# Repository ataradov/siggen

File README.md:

# SigGen

SigGen is a 100+ MHz signal generator (square wave only) and frequency counter based on Atmel SAM D11.

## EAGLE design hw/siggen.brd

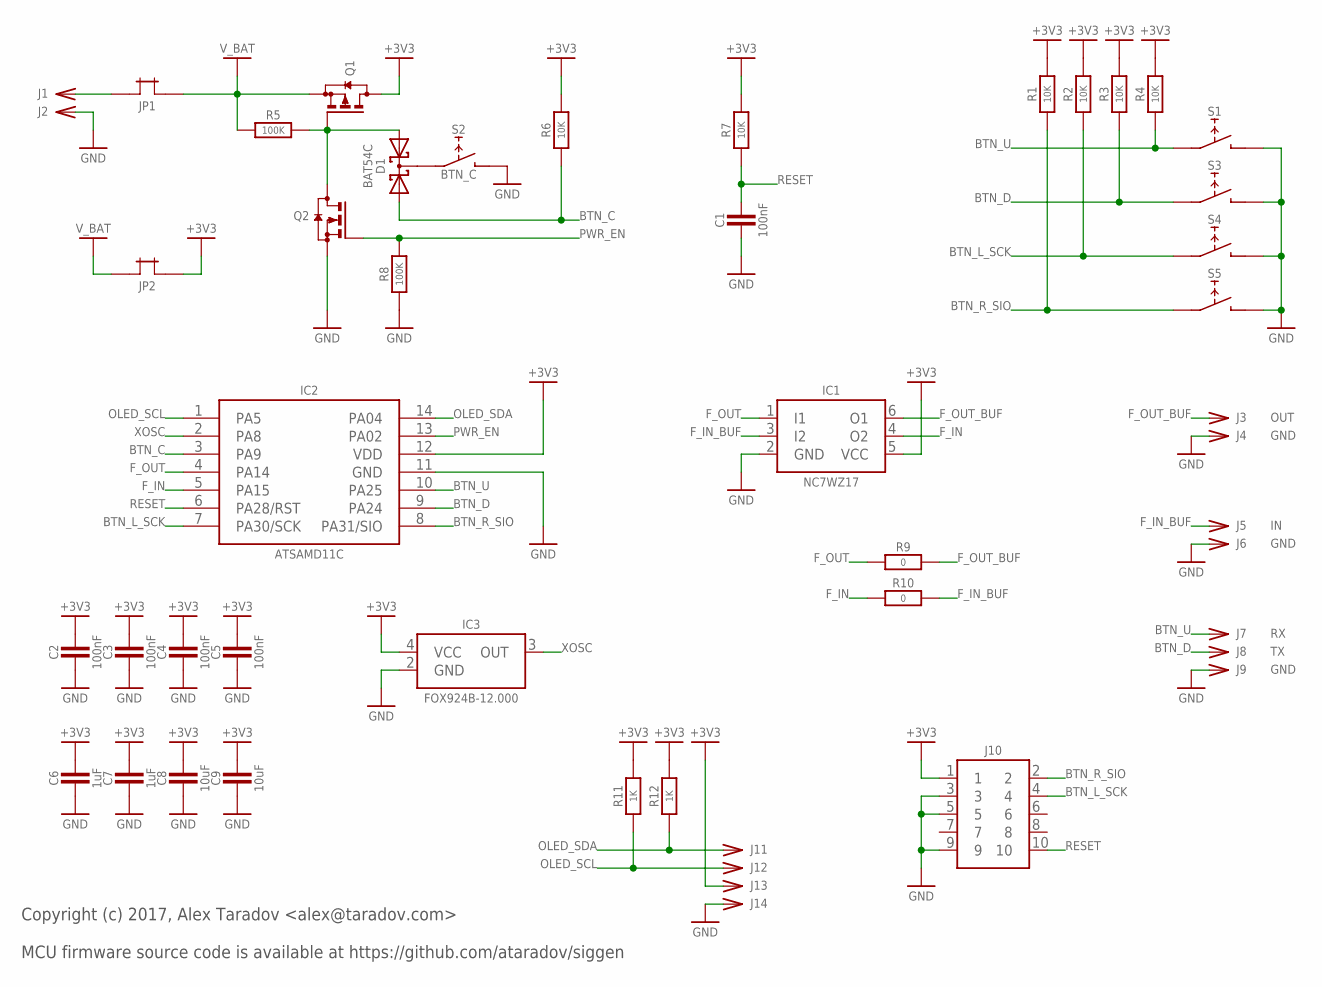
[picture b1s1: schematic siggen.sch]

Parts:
C1, C2, C3, C4, C5: 100nF; SMD0603
C6, C7: 1uF; SMD0603
C8, C9: 10uF; SMD0805
D1: BAT54C; SOT23
IC1: NC7WZ17; SC70
IC2: ATSAMD11C; SO-14
IC3: FOX924B-12.000; CTS406
J1, J2, J11, J12, J13, J14: CONN-SINGLE-TH; PIN-TH
J3: OUT; PIN-TH
J4, J6, J9: GND; PIN-TH
J5: IN; PIN-TH
J7: RX; PIN-TH
J8: TX; PIN-TH
J10: HEADER-5X2-TH-1.27; HEADER-5X2-1.27MM
JP1, JP2: JUMPER-TH-TH; JUMPER-TH
Q1: P-MOSFET; SOT23
Q2: N-MOSFET; SOT23
R1, R2, R3, R4, R6, R7: 10K; SMD0603
R5, R8: 100K; SMD0603
R9, R10: 0; SMD0603
R11, R12: 1K; SMD0603
S1, S3, S4, S5: TACT_SWITCH_6MM-SMD; TACT-SMD-6MM
S2: BTN_C; TACT-SMD-6MM

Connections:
+3V3: C2.2, C3.2, C4.2, C5.2, C6.2, C7.2, C8.2, C9.2, IC1.5 (VCC), IC2.12 (VDD), IC3.4 (VCC), J10.1, J13.1, JP2.2, Q1.3 (D), R1.2, R2.2, R3.2, R4.2, R6.2, R7.2, R11.2, R12.2
BTN_C: D1.1 (A1), IC2.3 (PA9), R6.1
BTN_D: IC2.9 (PA24), J8.1, R3.1, S3.1, S3.2 (1)
BTN_L_SCK: IC2.7 (PA30/SCK), J10.4, R2.1, S4.1, S4.2 (1)
BTN_R_SIO: IC2.8 (PA31/SIO), J10.2, R1.1, S5.1, S5.2 (1)
BTN_U: IC2.10 (PA25), J7.1, R4.1, S1.1, S1.2 (1)
F_IN: IC1.4 (O2), IC2.5 (PA15), R10.1
F_IN_BUF: IC1.3 (I2), J5.1, R10.2
F_OUT: IC1.1 (I1), IC2.4 (PA14), R9.1
F_OUT_BUF: IC1.6 (O1), J3.1, R9.2
GND: C1.1, C2.1, C3.1, C4.1, C5.1, C6.1, C7.1, C8.1, C9.1, IC1.2 (GND), IC2.11 (GND), IC3.2 (GND), J2.1, J4.1, J6.1, J9.1, J10.3, J10.5, J10.9, J14.1, Q2.2 (S), R8.1, S1.3 (2), S1.4 (2), S2.3 (2), S2.4 (2), S3.3 (2), S3.4 (2), S4.3 (2), S4.4 (2), S5.3 (2), S5.4 (2)
unnamed: D1.2 (A2), Q1.1 (G), Q2.3 (D), R5.2
unnamed: D1.3 (CC), S2.1, S2.2 (1)
unnamed: J1.1, JP1.1
OLED_SCL: IC2.1 (PA5), J12.1, R11.1
OLED_SDA: IC2.14 (PA04), J11.1, R12.1
PWR_EN: IC2.13 (PA02), Q2.1 (G), R8.2
RESET: C1.2, IC2.6 (PA28/RST), J10.10, R7.1
V_BAT: JP1.2, JP2.1, Q1.2 (S), R5.1
XOSC: IC2.2 (PA8), IC3.3 (OUT)

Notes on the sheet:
Copyright (c) 2017, Alex Taradov <alex@taradov.com> MCU firmware source code is available at https://github.com/ataradov/siggen

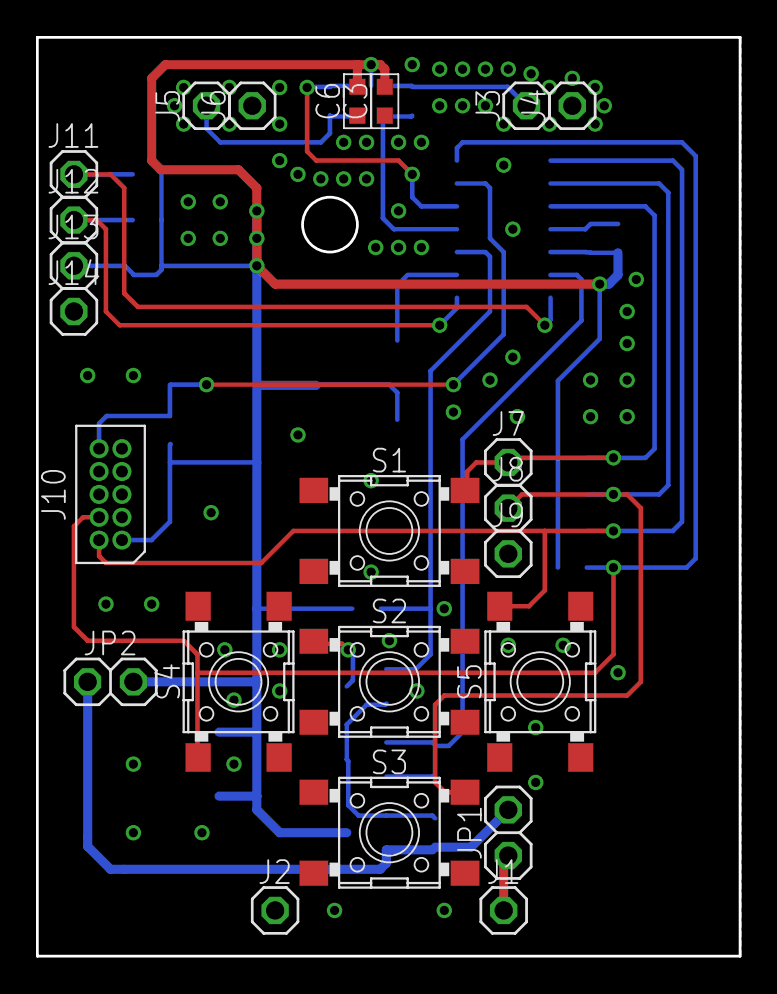
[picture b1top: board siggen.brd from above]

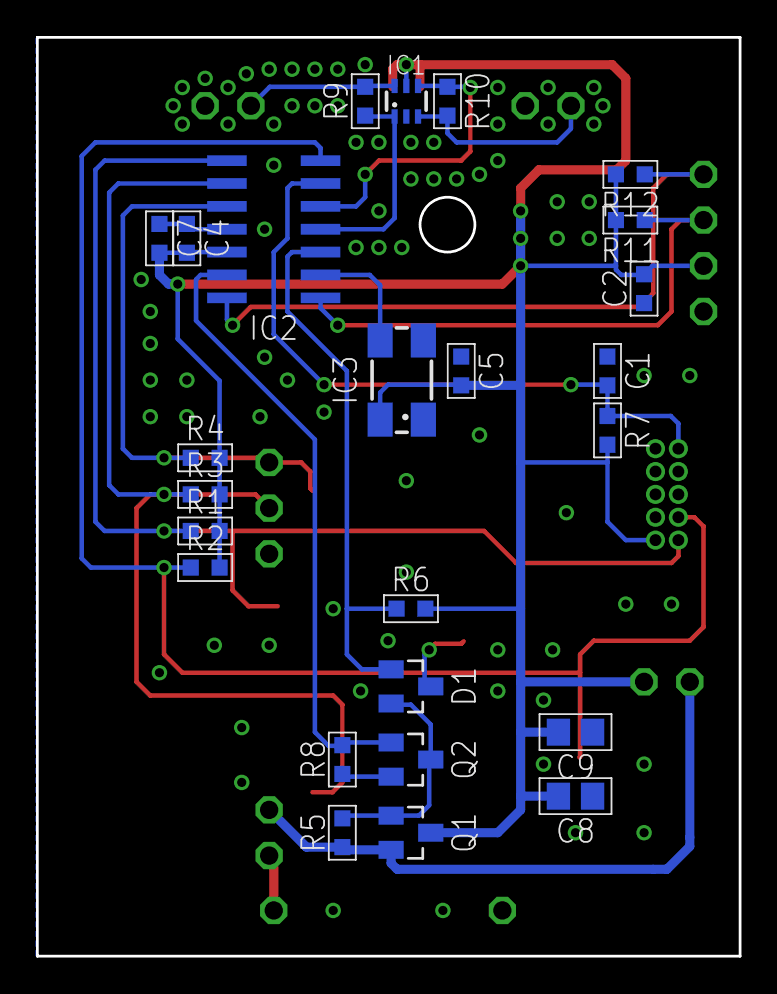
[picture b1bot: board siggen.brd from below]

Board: 2 copper layers, 39.0 x 51.0 mm, 48 parts (25 on the bottom side), 20 nets.

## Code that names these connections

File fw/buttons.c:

/*
 * Copyright (c) 2017, Alex Taradov <alex@taradov.com>
 * All rights reserved.
 *
 * Redistribution and use in source and binary forms, with or without
 * modification, are permitted provided that the following conditions are met:
 *
 * 1. Redistributions of source code must retain the above copyright notice,
 *    this list of conditions and the following disclaimer.
 * 2. Redistributions in binary form must reproduce the above copyright
 *    notice, this list of conditions and the following disclaimer in the
 *    documentation and/or other materials provided with the distribution.
 * 3. The name of the author may not be used to endorse or promote products
 *    derived from this software without specific prior written permission.
 *
 * THIS SOFTWARE IS PROVIDED BY THE COPYRIGHT HOLDERS AND CONTRIBUTORS "AS IS"
 * AND ANY EXPRESS OR IMPLIED WARRANTIES, INCLUDING, BUT NOT LIMITED TO, THE
 * IMPLIED WARRANTIES OF MERCHANTABILITY AND FITNESS FOR A PARTICULAR PURPOSE
 * ARE DISCLAIMED. IN NO EVENT SHALL THE COPYRIGHT HOLDER OR CONTRIBUTORS BE
 * LIABLE FOR ANY DIRECT, INDIRECT, INCIDENTAL, SPECIAL, EXEMPLARY, OR
 * CONSEQUENTIAL DAMAGES (INCLUDING, BUT NOT LIMITED TO, PROCUREMENT OF
 * SUBSTITUTE GOODS OR SERVICES; LOSS OF USE, DATA, OR PROFITS; OR BUSINESS
 * INTERRUPTION) HOWEVER CAUSED AND ON ANY THEORY OF LIABILITY, WHETHER IN
 * CONTRACT, STRICT LIABILITY, OR TORT (INCLUDING NEGLIGENCE OR OTHERWISE)
 * ARISING IN ANY WAY OUT OF THE USE OF THIS SOFTWARE, EVEN IF ADVISED OF THE
 * POSSIBILITY OF SUCH DAMAGE.
 */

/*- Includes ----------------------------------------------------------------*/
#include <stdint.h>
#include <stdbool.h>
#include <samd11.h>
#include "hal_gpio.h"
#include "buttons.h"
#include "globals.h"

/*- Definitions -------------------------------------------------------------*/
#define BUTTON_REPEAT_DELAY      200 // ms
#define BUTTON_REPEAT_INTERVAL   50 // ms

HAL_GPIO_PIN(BTN_U,    A, 25)
HAL_GPIO_PIN(BTN_D,    A, 24)
HAL_GPIO_PIN(BTN_L,    A, 30)
HAL_GPIO_PIN(BTN_R,    A, 31)
HAL_GPIO_PIN(BTN_C,    A, 9)

/* Proto
HAL_GPIO_PIN(BTN_U,    A, 25)
HAL_GPIO_PIN(BTN_D,    A, 31)
HAL_GPIO_PIN(BTN_L,    A, 2)
HAL_GPIO_PIN(BTN_R,    A, 30)
HAL_GPIO_PIN(BTN_C,    A, 24)
*/

/*- Variables ---------------------------------------------------------------*/
static bool buttons_state[N_BUTTONS];
static bool buttons_repeat[N_BUTTONS];
static int buttons_time[N_BUTTONS];

/*- Implementations ---------------------------------------------------------*/

//-----------------------------------------------------------------------------
void buttons_init(void)
{
  HAL_GPIO_BTN_U_in();
  HAL_GPIO_BTN_U_pullup();

  HAL_GPIO_BTN_D_in();
  HAL_GPIO_BTN_D_pullup();

  HAL_GPIO_BTN_L_in();
  HAL_GPIO_BTN_L_pullup();

  HAL_GPIO_BTN_R_in();
  HAL_GPIO_BTN_R_pullup();

  HAL_GPIO_BTN_C_in();
  HAL_GPIO_BTN_C_pullup();

  for (int i = 0; i < N_BUTTONS; i++)
  {
    buttons_state[i] = buttons_pressed(i);
    buttons_repeat[i] = false;
    buttons_time[i] = 0;
  }
}

//-----------------------------------------------------------------------------
bool buttons_pressed(int index)
{
  if (BUTTON_UP == index)
    return (0 == HAL_GPIO_BTN_U_read());
  else if (BUTTON_DOWN == index)
    return (0 == HAL_GPIO_BTN_D_read());
  else if (BUTTON_LEFT == index)
    return (0 == HAL_GPIO_BTN_L_read());
  else if (BUTTON_RIGHT == index)
    return (0 == HAL_GPIO_BTN_R_read());
  else if (BUTTON_RIGHT == index)
    return (0 == HAL_GPIO_BTN_R_read());
  else
    return (0 == HAL_GPIO_BTN_C_read());
}

//-----------------------------------------------------------------------------
void buttons_task(void)
{
  int sys_time = get_system_time();

  for (int i = 0; i < N_BUTTONS; i++)
  {
    bool new_state = buttons_pressed(i);
    int delta = sys_time - buttons_time[i];

    if (buttons_state[i])
    {
      int repeat_delta = buttons_repeat[i] ? BUTTON_REPEAT_INTERVAL : BUTTON_REPEAT_DELAY;

      if (delta > repeat_delta)
      {
        buttons_event(i, BUTTON_REPEAT, delta);
        buttons_time[i] = sys_time;
        buttons_repeat[i] = true;
      }
    }

    if (buttons_state[i] != new_state)
    {
      buttons_event(i, new_state ? BUTTON_PRESSED : BUTTON_RELEASED, delta);

      if (false == new_state)
        buttons_repeat[i] = false;

      buttons_state[i] = new_state;
      buttons_time[i] = sys_time;
    }
  }
}

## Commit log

2017-05-07 Minor cleanup
2017-05-07 Added PDF of the schematic
2020-05-13 Minor updates
